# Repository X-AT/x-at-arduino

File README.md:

X Antenna Tracker arduino daughter board
========================================

This board implements simple and dumb controller
for low level devices like stepper driver and endstops.

All communication done by custom USB HID class.

[![alpha version build on breadboard][img171]][blog]

[img171]: http://x-at.github.io/images/arduino-board/IMG171.jpg
[blog]: http://x-at.github.io/xat/2015/01/13/arduino-board.html

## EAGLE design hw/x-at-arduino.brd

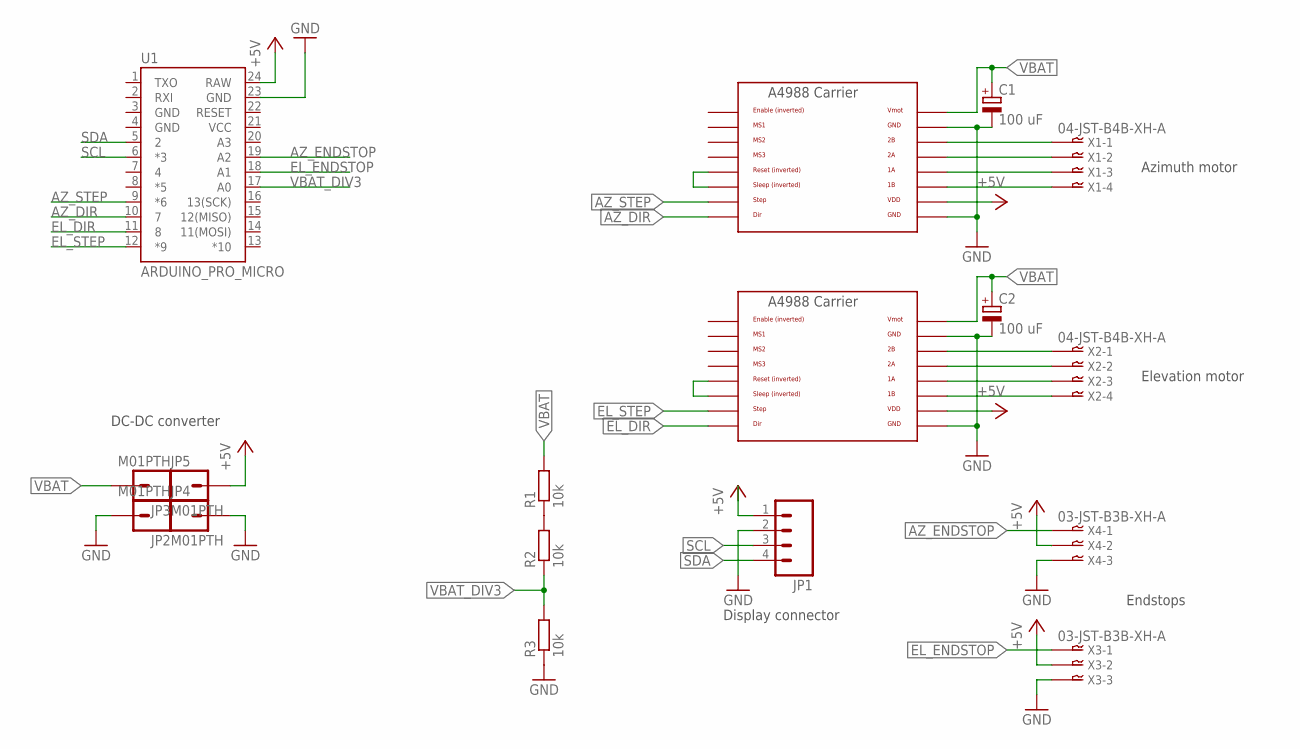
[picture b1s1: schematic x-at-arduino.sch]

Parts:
C1, C2: 100 uF; E5-6
JP1: M04PTH; 1X04
JP2, JP3, JP4, JP5: M01PTH; 1X01
R1, R2, R3: 10k; R0603
U1: ARDUINO_PRO_MICRO
U2, U3: POLOLU_A4983CARRIER; A4988BREAKOUT
X1, X2: 04-JST-B4B-XH-A; B4B-XH
X3, X4: 03-JST-B3B-XH-A; B3B-XH

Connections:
+5V: JP1.1, JP5.1, U1.24 (RAW), U2.VDD, U3.VDD, X3.P$2, X4.P$2
AZ_DIR: U1.10 (7), U2.DIR
AZ_ENDSTOP: U1.19 (A2), X4.P$1
AZ_STEP: U1.9 (*6), U2.STEP
EL_DIR: U1.11 (8), U3.DIR
EL_ENDSTOP: U1.18 (A1), X3.P$1
EL_STEP: U1.12 (*9), U3.STEP
GND: C1.-, C2.-, JP1.2, JP2.1, JP4.1, R3.1, U1.23 (GND), U2.GND, U2.GND@0 (GND), U3.GND, U3.GND@0 (GND), X3.P$3, X4.P$3
unnamed: U2.2B, X1.P$1
unnamed: U2.2A, X1.P$2
unnamed: U2.1A, X1.P$3
unnamed: U2.1B, X1.P$4
unnamed: U3.2B, X2.P$1
unnamed: U3.2A, X2.P$2
unnamed: U3.1A, X2.P$3
unnamed: U3.1B, X2.P$4
unnamed: R1.1, R2.2
unnamed: U3.RST, U3.SLP (SLEEP)
unnamed: U2.RST, U2.SLP (SLEEP)
SCL: JP1.3, U1.6 (*3)
SDA: JP1.4, U1.5 (2)
VBAT: C1.+, C2.+, JP3.1, R1.2, U2.VMOT, U3.VMOT
VBAT_DIV3: R2.1, R3.2, U1.17 (A0)

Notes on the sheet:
Display connector
Endstops
Azimuth motor
Elevation motor
DC-DC converter

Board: 2 copper layers, 17 parts (0 on the bottom side), 23 nets, no tracks yet.

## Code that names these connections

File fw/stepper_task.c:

#include "main.h"
#include "accelstepper.h"

#define EL_STEP		PB5
#define EL_DIR		PB4
#define AZ_STEP		PD7
#define AZ_DIR		PE6
#define step_pulse_delay()	_delay_us(1)

#define INIT_ACCEL	50
#define INIT_MSPEED	200

static AccelStepper_t azimuth_stepper,
		      elevation_stepper;

static void azimuth_step(AccelStepper_t *self)
{
	cbi(PORTD, AZ_STEP);

	if (self->direction == DIRECTION_CCW)
		sbi(PORTE, AZ_DIR);
	else
		cbi(PORTE, AZ_DIR);

	sbi(PORTD, AZ_STEP);
	step_pulse_delay();
	cbi(PORTD, AZ_STEP);
}

static void elevation_step(AccelStepper_t *self)
{
	cbi(PORTB, EL_STEP);

	if (self->direction == DIRECTION_CCW)
		sbi(PORTB, EL_DIR);
	else
		cbi(PORTB, EL_DIR);

	sbi(PORTB, EL_STEP);
	step_pulse_delay();
	cbi(PORTB, EL_STEP);
}

void Stepper_Task_Init(void)
{
	// GPIO setup
	cbi(PORTB, EL_STEP);
	cbi(PORTB, EL_DIR);
	sbi(DDRB, EL_STEP);
	sbi(DDRB, EL_DIR);

	cbi(PORTD, AZ_STEP);
	cbi(PORTE, AZ_DIR);
	sbi(DDRD, AZ_STEP);
	sbi(DDRE, AZ_DIR);

	AS_ObjectInit(&azimuth_stepper, azimuth_step);
	AS_ObjectInit(&elevation_stepper, elevation_step);

	AS_SetAcceleration(&azimuth_stepper, INIT_ACCEL);
	AS_SetAcceleration(&elevation_stepper, INIT_ACCEL);
	AS_SetMaxSpeed(&azimuth_stepper, INIT_MSPEED);
	AS_SetMaxSpeed(&elevation_stepper, INIT_MSPEED);
}

void Stepper_Task(void)
{
	AS_Run(&azimuth_stepper);
	AS_Run(&elevation_stepper);
}

int32_t Stepper_GetAzPosition(void)
{
	return AS_CurrentPosition(&azimuth_stepper);
}

int32_t Stepper_GetElPosition(void)
{
	return AS_CurrentPosition(&elevation_stepper);
}

uint8_t Stepper_GetFlags(void)
{
	uint8_t flags = 0;

	if (AS_DistanceToGo(&azimuth_stepper) != 0)
		flags |= FLAGS_AZ_IN_MOTION;

	if (AS_DistanceToGo(&elevation_stepper) != 0)
		flags |= FLAGS_EL_IN_MOTION;

	return flags;
}

void Stepper_GetSettings(struct XAT_Report_Stepper_Settings *settings)
{
	// Should i add accesor wrapper?
	settings->azimuth_acceleration = azimuth_stepper.acceleration;
	settings->elevation_acceleration = elevation_stepper.acceleration;
	settings->azimuth_max_speed = azimuth_stepper.max_speed;
	settings->elevation_max_speed = elevation_stepper.max_speed;
}

void Stepper_SetSettings(const struct XAT_Report_Stepper_Settings *settings)
{
	AS_SetAcceleration(&azimuth_stepper, settings->azimuth_acceleration);
	AS_SetMaxSpeed(&azimuth_stepper, settings->azimuth_max_speed);
	AS_SetAcceleration(&elevation_stepper, settings->elevation_acceleration);
	AS_SetMaxSpeed(&elevation_stepper, settings->elevation_max_speed);
}

void Stepper_SetAzEl(const struct XAT_Report_Az_El *az_el)
{
	AS_MoveTo(&azimuth_stepper, az_el->azimuth_position);
	AS_MoveTo(&elevation_stepper, az_el->elevation_position);
}

void Stepper_SetCurPosition(const struct XAT_Report_Cur_Position *cur_position)
{
	AS_SetCurrentPosition(&azimuth_stepper, cur_position->azimuth_position);
	AS_SetCurrentPosition(&elevation_stepper, cur_position->elevation_position);
}

void Stepper_Stop(bool az, bool el)
{
	if (az)
		AS_Stop(&azimuth_stepper);

	if (el)
		AS_Stop(&elevation_stepper);
}

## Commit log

2015-01-13 Import eagle files
2015-01-13 try to use Eagle description
2015-01-13 hw: readme again
2015-01-13 hw: github don't support html, try markdown
2015-01-13 hw: try not use hardlink
2015-01-14 fw: Import LUFA 140928
2015-01-14 fw: Import initial HID firmware.
    Based on GenericHID demo.
2015-01-14 fw: Initial add HID descripter generated by Dt.exe
2015-01-14 fw: Add reports for stepper and qtr.
2015-01-14 fw: Enable BAT VOLTAGE report.
2015-01-14 fw: Enable QTR report.
    I decided to replace QTR-1RC with QTR-1A (replace capacitor->resistor).
2015-01-14 fw: Port AccelStepper to C. Not tested.
    TODO: monotonic microsecond timer.
2015-01-14 fw: Import wall_time module for micros()/millis().
2015-01-14 fw: Add stepper_task module. Not tested.
2015-01-14 fw: Enable stepper reports. tested.
    accelstepper.c works like a charm.
2015-01-15 fw: Enable WDT. Fix #2
2015-01-15 fw: Add error indication on LED1.
2015-01-15 Add GPLv3 license.
2015-01-15 fw: Add git version to USB SerialNumber string.
    Prepare first repease 0.1.0.
2015-01-15 fw: Import U8glib 1.17
    This library will be used for SSD1306 OLED display.
2015-01-15 fw: Add display hello world.
2015-01-15 fw: Show usb status messages on display.
2015-01-15 fw: Add reports for setting position and stop motors
2015-01-15 fw: Add reports for display write 8, 16, 32 and 60 bytes.
    Issue #1
2015-01-15 fw #1: Implement display drawing reports.
2015-01-15 hw: Note that now used analog sensor on endstop.
2015-01-15 fw: Remove display support (breaks stepper).
    Close #1.
2015-01-15 fw: Release 0.2.0. All devices works.
2015-01-15 binary: Save firmware version 0.2.0
2015-01-17 fw: Fix IN_MOTION flags.
2015-01-17 Prepare 0.2.1 (bugfix release)
2015-01-17 binary: prebuild binary for release 0.2.1
2015-01-29 Apply my new VID/PID pair, fix version string.
    Thank to OpenMoko Inc!
2015-01-29 Add precompilled 0.3.0 version.

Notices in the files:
parts and their libraries:
SparkFun-Connectors: Licensing: Creative Commons ShareAlike 4.0 International - https://creativecommons.org/licenses/by-sa/4.0
SparkFun-Boards: Licensing: CC v3.0 Share-Alike You are welcome to use this library for commercial purposes.
